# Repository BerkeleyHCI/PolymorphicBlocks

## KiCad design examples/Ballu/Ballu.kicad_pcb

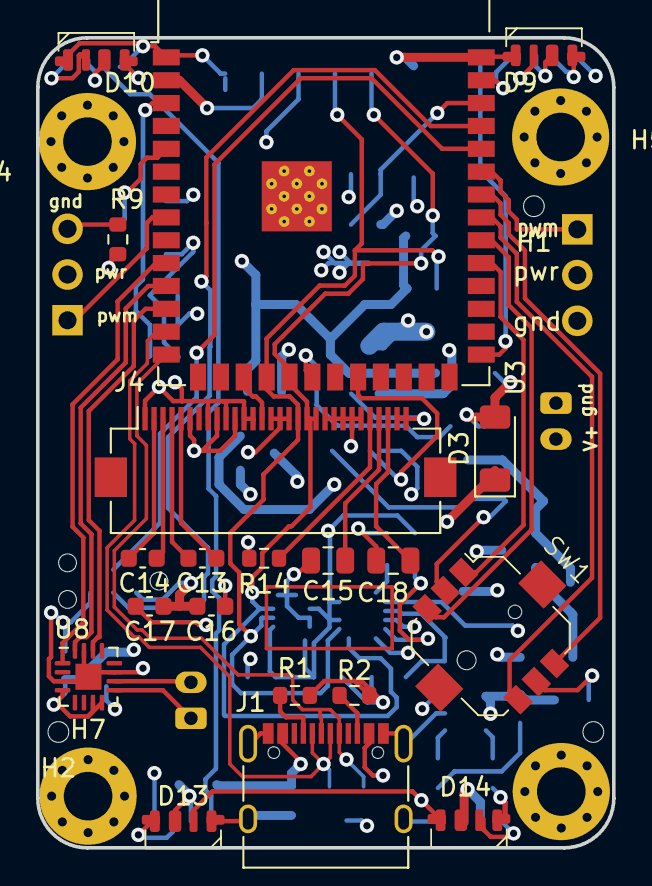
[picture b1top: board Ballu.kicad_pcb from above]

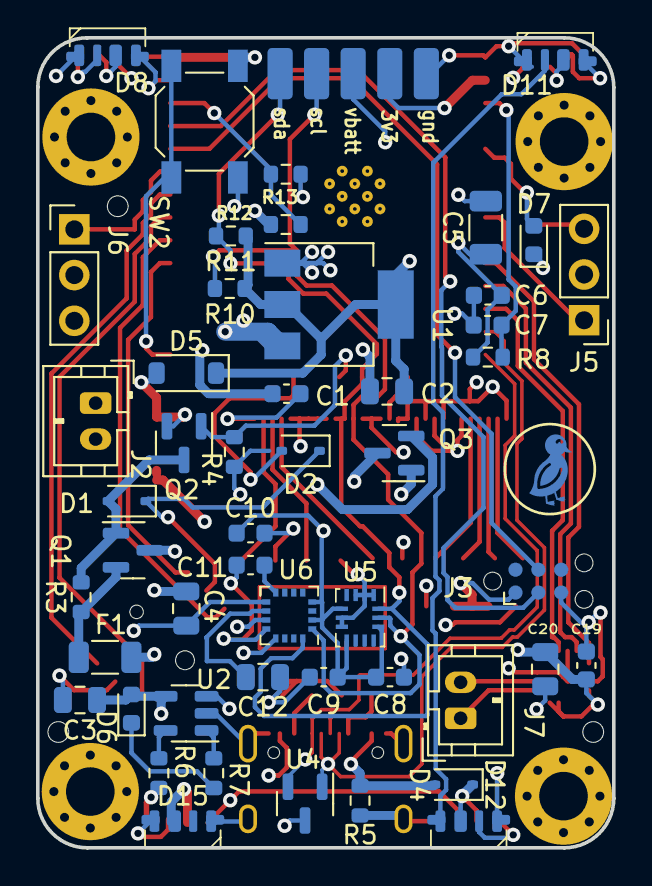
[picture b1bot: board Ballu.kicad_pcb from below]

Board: 4 copper layers, 32.0 x 45.0 mm, 83 parts (55 on the bottom side), 57 nets.

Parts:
C1, C6, C7, C8, C9, C10, C11, C13, C14, C16, C17, C19: C_0603_1608Metric
C2, C3, C4, C12, C15, C18, C20: C_0805_2012Metric
C5: C_1206_3216Metric
D1, D2: 30V 370mV@1mA 30mA SOD-323 Schottky Barrier Diode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; D_SOD-323
D3: D_MiniMELF
D4: 10V 1V@600mA 3A SOD-323 Schottky Barrier Diodes (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; D_SOD-323
D5: 5?A@1V 90? Single 3.6V~3.8V 350mW 3.4V SOD-123 Ze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; D_SOD-123
D6: LED_0603_1608Metric
D7: Red 615~630nm 1.9~2.2V 0603 Light Emitting Diodes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; LED_0603_1608Metric
D8, D9, D10, D11, D12, D13, D14, D15: SK6812 SIDE-A; LED_SK6812-SIDE-A
F1: 6V 2A 100A 4A 1206 Resettable Fuses ROHS; R_1206_3216Metric
H1, H2, H3: JlcToolingHole_1.152mm
H4, H5, H6, H7: M2.5; MountingHole_2.7mm_M2.5_Pad_Via
J1: COM-15111; USB_C_Receptacle_XKB_U262-16XN-4BVC11
J2, J7: B2B-PH-K; JST_PH_B2B-PH-K_1x02_P2.00mm_Vertical
J3: Tag-Connect_TC2030-IDC-NL_2x03_P1.27mm_Vertical
J4: AFC01-S30FCA-00; Hirose_FH12-30S-0.5SH_1x30-1MP_P0.50mm_Horizontal
J5, J6: PinHeader2.54 1x3; PinHeader_1x03_P2.54mm_Vertical
Q1: 20V 3.1A 860mW 112m?@4.5V,2.8A 1V@250?A P Channel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; SOT-23
Q2: 60V 115mA 200mW 7.5?@10V,500mA 2.5V@250?A N Chann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; SOT-23
Q3: 30V 4A 44m?@10V,4.3A 1.4W 1.3V@250?A P Channel SO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; SOT-23
R1, R2, R3, R4, R5, R6, R7, R8, R9, R10, R11, R12, R13, R14: R_0603_1608Metric
SW1: SKRHABE010; DirectionSwitch_Alps_SKRH
SW2: 5.1mm switch; SW_SPST_SKQG_WithoutStem
TP1: gnd; TestPoint_TE_RCT_0805
TP2: gate.vbatt; TestPoint_TE_RCT_0805
TP3: preg_3v3._pwr_out_link; TestPoint_TE_RCT_0805
TP4: i2c.scl; TestPoint_TE_RCT_0805
TP5: i2c.sda; TestPoint_TE_RCT_0805
U1: LDL1117S33R; SOT-223-3_TabPin2
U2: MCP73831T-2ACI/OT; SOT-23-5
U3: ESP32-S3-WROOM-1-N16R8; ESP32-S3-WROOM-1
U4: PESD5V0X1BT; SOT-23
U5: LSM6DS3TR-C; Bosch_LGA-14_3x2.5mm_P0.5mm
U6: QMC5883L; LGA-16_3x3mm_P0.5mm
U7: ER-OLED-0.96-1.1; Lcd_Er_Oled0.96_1.1_Outline
U8: MAX98357AETE+T; QFN-16-1EP_3x3mm_P0.5mm_EP1.45x1.45mm
svg2mod: G***; Symbol_DucklingSolid

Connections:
batt.pwr: C4.1, F1.1, J2.2, U2.3
batt_sense.output: R12.2, R13.1, U3.38
charger.charge_led.res.a: D6.1, R7.1
charger.charge_led.signal: R7.2, U2.1
charger.charger.prog_res.a: R6.1, U2.5
gate.btn_out: D2.2, U3.22
gate.control: Q2.1, R4.2, U3.20
gate.dir.center: D1.1, D2.1, SW1.2
gate.dir_a: SW1.1, U3.31
gate.dir_b: SW1.4, U3.34
gate.dir_c: SW1.3, U3.32
gate.dir_d: SW1.6, U3.33
gate.fuse.pwr_out: F1.2, Q1.2, R3.1
gate.gate.pull_res.b: D1.2, Q1.1, Q2.3, R3.2
gate.vbatt: D3.1, Q1.3, Q3.3, TP2.1
gnd: C1.2, C2.2, C3.2, C4.2, C5.2, C6.2, C7.2, C8.2, C9.2, C10.2, C12.2, C15.2, C16.2, C17.2, C18.2, C19.2, C20.2, D3.2, D5.2, D8.4, D9.4, D10.4, D11.4, D12.4, D13.4, D14.4, D15.4, J1.A1, J1.A12, J1.B1, J1.B12, J1.S1, J2.1, J3.5, J4.1, J4.8, J4.10, J4.12, J4.13, J4.15, J4.16, J4.17, J4.21, J4.22, J4.23, J4.24, J4.25, J4.29, J4.30, J5.3, J6.3, Q2.2, R1.1, R2.1, R4.1, R5.2, R6.2, R9.2, R13.2, R14.2, SW1.5, SW2.2, TP1.1, U1.1, U2.2, U3.1, U3.40, U3.41, U4.3, U5.1, U5.2, U5.3, U5.6, U5.7, U6.9, U6.11, U8.3, U8.11, U8.15, U8.17
i2c_chain_0.scl: J4.18, R10.2, TP4.1, U3.18, U5.13, U6.1
i2c_chain_0.sda: J4.19, J4.20, R11.2, TP5.1, U3.19, U5.14, U6.16
led.res.a: D7.1, R9.1
led.signal: D7.2, U3.5
mag.c1.pos: C12.1, U6.10
mag.set_cap.neg: C11.2, U6.12
mag.set_cap.pos: C11.1, U6.8
mcu.program_boot_node: SW2.1, U3.27
mcu.program_en_node: C7.1, R8.2, U3.3
mcu.program_uart_node.a_tx: J3.3, U3.37
mcu.program_uart_node.b_tx: J3.4, U3.36
npx_side.din: D8.1, U3.39
npx_side.led[0].dout: D8.3, D9.1
npx_side.led[1].dout: D9.3, D10.1
npx_side.led[2].dout: D10.3, D11.1
npx_side.led[3].dout: D11.3, D12.1
npx_side.led[4].dout: D12.3, D13.1
npx_side.led[5].dout: D13.3, D14.1
npx_side.led[6].dout: D14.3, D15.1
oled.c1_cap.neg: C13.2, J4.5
oled.c1_cap.pos: C13.1, J4.4
oled.c2_cap.neg: C14.2, J4.3
oled.c2_cap.pos: C14.1, J4.2
oled.device.vcc: C18.1, J4.28
oled.device.vcomh: C15.1, J4.27
oled.iref_res.a: J4.26, R14.1
oled.reset: J4.14, U3.17
pwr: C1.1, D4.1, D8.2, D9.2, D10.2, D11.2, D12.2, D13.2, D14.2, D15.2, J5.2, J6.2, Q3.2, R12.1, U1.3
servo[0].pwm: J5.1, U3.8
servo[1].pwm: J6.1, U3.35
spk_drv.i2s.sck: U3.11, U8.16
spk_drv.i2s.sd: U3.10, U8.1
spk_drv.i2s.ws: U3.12, U8.14
spk_drv.out.a: J7.1, U8.9
spk_drv.out.b: J7.2, U8.10
usb.conn.A5: J1.A5, R1.2
usb.conn.B5: J1.B5, R2.2
usb_chain_0.d_N: J1.A7, J1.B7, U3.13, U4.1
usb_chain_0.d_P: J1.A6, J1.B6, U3.14, U4.2
v3v3: C2.1, C5.1, C6.1, C8.1, C9.1, C10.1, C16.1, C17.1, C19.1, C20.1, D5.1, J3.1, J4.6, J4.9, J4.11, R8.1, R10.1, R11.1, TP3.1, U1.2, U3.2, U5.5, U5.8, U5.12, U6.2, U6.4, U6.13, U8.4, U8.7, U8.8
vusb: C3.1, D4.2, D6.2, J1.A4, J1.A9, J1.B4, J1.B9, Q3.1, R5.1, U2.4

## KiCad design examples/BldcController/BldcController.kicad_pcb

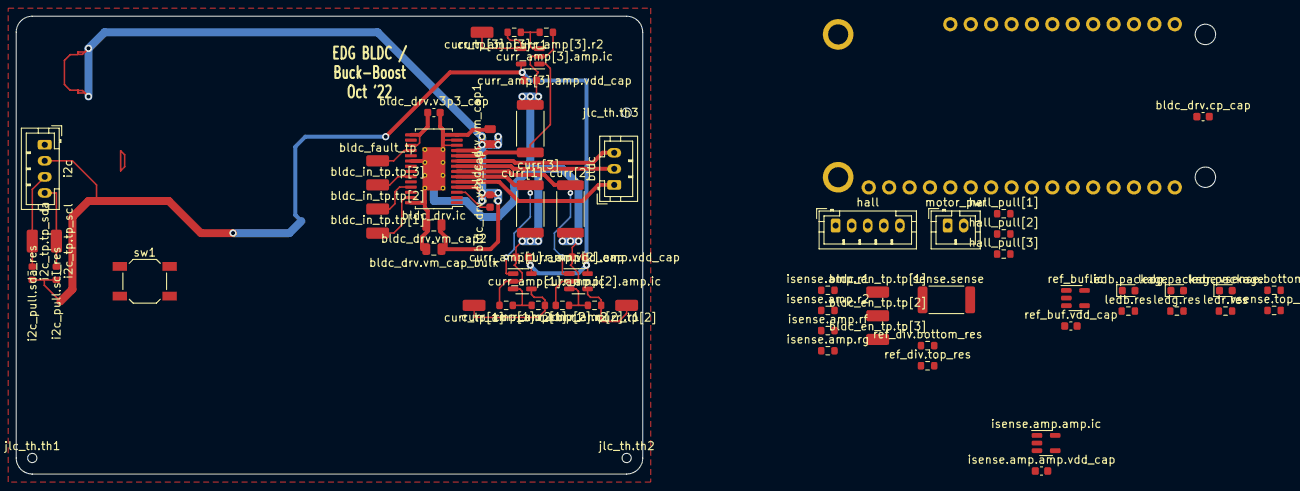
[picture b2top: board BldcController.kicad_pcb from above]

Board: 2 copper layers, 78.0 x 57.0 mm, 67 parts (0 on the bottom side), 47 nets.

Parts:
bldc: B3B-PH-K (JST); JST_PH_B3B-PH-K_1x03_P2.00mm_Vertical
bldc_drv.cp_cap, bldc_drv.v3p3_cap, bldc_drv.vcp_cap: C_0603_1608Metric
bldc_drv.ic: DRV8313PWP (Texas Instruments); HTSSOP-28-1EP_4.4x9.7mm_P0.65mm_EP2.85x5.4mm_ThermalVias
bldc_drv.vm_cap1, bldc_drv.vm_cap2, bldc_drv.vm_cap_bulk: C_0805_2012Metric
bldc_en_tp.tp[1]: 5015 (Keystone) - _mcu_gpio_bldc_en_link.1; TestPoint_TE_RCT_0805
bldc_en_tp.tp[2]: 5015 (Keystone) - _mcu_gpio_bldc_en_link.2; TestPoint_TE_RCT_0805
bldc_en_tp.tp[3]: 5015 (Keystone) - _mcu_gpio_bldc_en_link.3; TestPoint_TE_RCT_0805
bldc_fault_tp: 5015 (Keystone) - _mcu_gpio_bldc_fault_link; TestPoint_TE_RCT_0805
bldc_in_tp.tp[1]: 5015 (Keystone) - _mcu_gpio_bldc_in_link.1; TestPoint_TE_RCT_0805
bldc_in_tp.tp[2]: 5015 (Keystone) - _mcu_gpio_bldc_in_link.2; TestPoint_TE_RCT_0805
bldc_in_tp.tp[3]: 5015 (Keystone) - _mcu_gpio_bldc_in_link.3; TestPoint_TE_RCT_0805
curr[1], curr[2], curr[3]: R_2512_6332Metric
curr_amp[1].amp.ic, curr_amp[2].amp.ic, curr_amp[3].amp.ic: LMV321 (Texas Instruments); SOT-23-5
curr_amp[1].amp.vdd_cap, curr_amp[2].amp.vdd_cap, curr_amp[3].amp.vdd_cap: C_0603_1608Metric
curr_amp[1].r1, curr_amp[1].r2, curr_amp[2].r1, curr_amp[2].r2, curr_amp[3].r1, curr_amp[3].r2: R_0603_1608Metric
curr_tp[1]: 5015 (Keystone) - _curr_amp[1]_output_link; TestPoint_TE_RCT_0805
curr_tp[2]: 5015 (Keystone) - _curr_amp[2]_output_link; TestPoint_TE_RCT_0805
curr_tp[3]: 5015 (Keystone) - _curr_amp[3]_output_link; TestPoint_TE_RCT_0805
hall: B5B-PH-K (JST); JST_PH_B5B-PH-K_1x05_P2.00mm_Vertical
hall_pull[1], hall_pull[2], hall_pull[3]: R_0603_1608Metric
i2c: B4B-PH-K (JST); JST_PH_B4B-PH-K_1x04_P2.00mm_Vertical
i2c_pull.scl_res, i2c_pull.sda_res: R_0603_1608Metric
i2c_tp.tp_scl: 5015 (Keystone) - _mcu_i2c_i2c_link.scl; TestPoint_TE_RCT_0805
i2c_tp.tp_sda: 5015 (Keystone) - i2c_tp._io_sda_link; TestPoint_TE_RCT_0805
isense.amp.amp.ic: LMV321 (Texas Instruments); SOT-23-5
isense.amp.amp.vdd_cap: C_0603_1608Metric
isense.amp.r1, isense.amp.r2, isense.amp.rf, isense.amp.rg: R_0603_1608Metric
isense.sense: R_2512_6332Metric
jlc_th.th1, jlc_th.th2, jlc_th.th3: JlcToolingHole_1.152mm
ledb.package: LED_0603_1608Metric
ledb.res: R_0603_1608Metric
ledg.package: LED_0603_1608Metric
ledg.res: R_0603_1608Metric
ledr.package: KT-0603R (Hubei KENTO Elec) - Red 615~630nm 1.9~2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; LED_0603_1608Metric
ledr.res: R_0603_1608Metric
mcu: Feather nRF52840 Express (Adafruit); FEATHERWING_NODIM
motor_pwr: B2B-PH-K (JST); JST_PH_B2B-PH-K_1x02_P2.00mm_Vertical
ref_buf.ic: LMV321 (Texas Instruments); SOT-23-5
ref_buf.vdd_cap: C_0603_1608Metric
ref_div.bottom_res, ref_div.top_res: R_0603_1608Metric
sw1: 5.1mm switch; SW_SPST_SKQG_WithoutStem
vsense.bottom_res, vsense.top_res: R_0603_1608Metric

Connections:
bldc_drv.cp_cap.neg: bldc_drv.cp_cap.2, bldc_drv.ic.1
bldc_drv.cp_cap.pos: bldc_drv.cp_cap.1, bldc_drv.ic.2
bldc_drv.ic.v3p3: bldc_drv.ic.15, bldc_drv.ic.17, bldc_drv.v3p3_cap.1
bldc_drv.nfault: bldc_drv.ic.18, bldc_fault_tp.1, mcu.18
bldc_drv.nreset: bldc_drv.ic.16, mcu.25
bldc_drv.outs.1: bldc.1, bldc_drv.ic.5
bldc_drv.outs.2: bldc.2, bldc_drv.ic.8
bldc_drv.outs.3: bldc.3, bldc_drv.ic.9
bldc_drv.vcp_cap.pos: bldc_drv.ic.3, bldc_drv.vcp_cap.1
curr[1].pwr_out: bldc_drv.ic.6, curr[1].2, curr_amp[1].amp.ic.1
curr[2].pwr_out: bldc_drv.ic.7, curr[2].2, curr_amp[2].amp.ic.1
curr[3].pwr_out: bldc_drv.ic.10, curr[3].2, curr_amp[3].amp.ic.1
curr_amp[1].output: curr_amp[1].amp.ic.4, curr_amp[1].r1.1, curr_tp[1].1, mcu.7
curr_amp[1].r1.b: curr_amp[1].amp.ic.3, curr_amp[1].r1.2, curr_amp[1].r2.1
curr_amp[2].output: curr_amp[2].amp.ic.4, curr_amp[2].r1.1, curr_tp[2].1, mcu.8
curr_amp[2].r1.b: curr_amp[2].amp.ic.3, curr_amp[2].r1.2, curr_amp[2].r2.1
curr_amp[3].output: curr_amp[3].amp.ic.4, curr_amp[3].r1.1, curr_tp[3].1, mcu.10
curr_amp[3].r1.b: curr_amp[3].amp.ic.3, curr_amp[3].r1.2, curr_amp[3].r2.1
gnd: bldc_drv.ic.12, bldc_drv.ic.13, bldc_drv.ic.14, bldc_drv.ic.20, bldc_drv.ic.28, bldc_drv.ic.29, bldc_drv.v3p3_cap.2, bldc_drv.vm_cap1.2, bldc_drv.vm_cap2.2, bldc_drv.vm_cap_bulk.2, curr[1].1, curr[2].1, curr[3].1, curr_amp[1].amp.ic.2, curr_amp[1].amp.vdd_cap.2, curr_amp[1].r2.2, curr_amp[2].amp.ic.2, curr_amp[2].amp.vdd_cap.2, curr_amp[2].r2.2, curr_amp[3].amp.ic.2, curr_amp[3].amp.vdd_cap.2, curr_amp[3].r2.2, hall.5, i2c.1, isense.amp.amp.ic.2, isense.amp.amp.vdd_cap.2, ledb.res.2, ledg.res.2, ledr.res.2, mcu.4, motor_pwr.1, ref_buf.ic.2, ref_buf.vdd_cap.2, ref_div.bottom_res.2, sw1.2, vsense.bottom_res.2
hall.u: hall.2, hall_pull[1].2, mcu.20
hall.v: hall.3, hall_pull[2].2, mcu.24
hall.w: hall.4, hall_pull[3].2, mcu.19
i2c_pull.i2c.scl: i2c.4, i2c_pull.scl_res.2, i2c_tp.tp_scl.1, mcu.21
i2c_pull.i2c.sda: i2c.3, i2c_pull.sda_res.2, i2c_tp.tp_sda.1, mcu.22
isense.amp.r1.b: isense.amp.amp.ic.3, isense.amp.r1.2, isense.amp.rf.2
isense.amp.r2.b: isense.amp.amp.ic.1, isense.amp.r2.2, isense.amp.rg.2
isense.out: isense.amp.amp.ic.4, isense.amp.rf.1, mcu.9
isense.pwr_out: bldc_drv.ic.4, bldc_drv.ic.11, bldc_drv.vcp_cap.2, bldc_drv.vm_cap1.1, bldc_drv.vm_cap2.1, bldc_drv.vm_cap_bulk.1, isense.amp.r1.1, isense.sense.2
isense.ref: isense.amp.rg.1, ref_buf.ic.3, ref_buf.ic.4
ledb.res.a: ledb.package.1, ledb.res.1
ledb.signal: ledb.package.2, mcu.23
ledg.res.a: ledg.package.1, ledg.res.1
ledg.signal: ledg.package.2, mcu.6
ledr.res.a: ledr.package.1, ledr.res.1
ledr.signal: ledr.package.2, mcu.16
mcu.gpio.bldc_en_1: bldc_drv.ic.26, bldc_en_tp.tp[1].1, mcu.17
mcu.gpio.bldc_en_2: bldc_drv.ic.24, bldc_en_tp.tp[2].1, mcu.11
mcu.gpio.bldc_en_3: bldc_drv.ic.22, bldc_en_tp.tp[3].1, mcu.15
mcu.gpio.bldc_in_1: bldc_drv.ic.27, bldc_in_tp.tp[1].1, mcu.12
mcu.gpio.bldc_in_2: bldc_drv.ic.25, bldc_in_tp.tp[2].1, mcu.13
mcu.gpio.bldc_in_3: bldc_drv.ic.23, bldc_in_tp.tp[3].1, mcu.14
motor_pwr.pwr: isense.amp.r2.1, isense.sense.1, motor_pwr.2, vsense.top_res.1
ref_div.output: ref_buf.ic.1, ref_div.bottom_res.1, ref_div.top_res.2
sw1.out: mcu.5, sw1.1
v3v3: curr_amp[1].amp.ic.5, curr_amp[1].amp.vdd_cap.1, curr_amp[2].amp.ic.5, curr_amp[2].amp.vdd_cap.1, curr_amp[3].amp.ic.5, curr_amp[3].amp.vdd_cap.1, hall_pull[1].1, hall_pull[2].1, hall_pull[3].1, i2c.2, i2c_pull.scl_res.1, i2c_pull.sda_res.1, isense.amp.amp.ic.5, isense.amp.amp.vdd_cap.1, mcu.2, ref_buf.ic.5, ref_buf.vdd_cap.1, ref_div.top_res.1
vsense.output: mcu.3, vsense.bottom_res.1, vsense.top_res.2
vusb: hall.1, mcu.26

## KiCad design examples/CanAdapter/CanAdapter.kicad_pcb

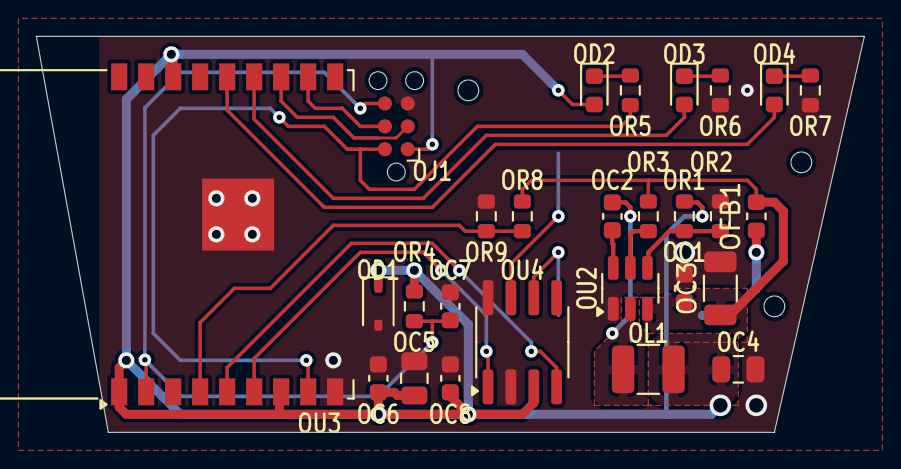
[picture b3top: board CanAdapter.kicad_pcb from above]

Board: 2 copper layers, 46.0 x 22.0 mm, 31 parts (1 on the bottom side), 22 nets.

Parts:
OC1: reg_3v3.hf_in_cap; C_0603_1608Metric
OC2: reg_3v3.boot_cap; C_0603_1608Metric
OC3: reg_3v3.power_path.in_cap; C_1206_3216Metric
OC4: reg_3v3.power_path.out_cap; C_0805_2012Metric
OC5: mcu.vcc_cap0; C_0805_2012Metric
OC6: mcu.vcc_cap1; C_0603_1608Metric
OC7: mcu.en_pull.c; C_0603_1608Metric
OC8: can.vdd_cap; C_0603_1608Metric
OD1: prot_3v3; D_SOD-323
OD2: ledr.package; LED_0603_1608Metric
OD3: ledg.package; LED_0603_1608Metric
OD4: ledw.package; LED_0603_1608Metric
OFB1: ferrite; L_0603_1608Metric
OH1: jlc_th.th1; JlcToolingHole_1.152mm
OH2: jlc_th.th2; JlcToolingHole_1.152mm
OH3: jlc_th.th3; JlcToolingHole_1.152mm
OJ1: mcu.prog; Tag-Connect_TC2030-IDC-NL_2x03_P1.27mm_Vertical
OL1: reg_3v3.power_path.inductor; L_1210_3225Metric
OR1: reg_3v3.fb.top_res; R_0603_1608Metric
OR2: reg_3v3.fb.bottom_res; R_0603_1608Metric
OR3: reg_3v3.en_res; R_0603_1608Metric
OR4: mcu.en_pull.r; R_0603_1608Metric
OR5: ledr.res; R_0603_1608Metric
OR6: ledg.res; R_0603_1608Metric
OR7: ledw.res; R_0603_1608Metric
OR8: vobd_sense.top_res; R_0603_1608Metric
OR9: vobd_sense.bottom_res; R_0603_1608Metric
OU1: obd; J1962
OU2: reg_3v3.ic; SOT-23-6
OU3: mcu.ic; ESP-WROOM-02
OU4: can.ic; SOIC-8_3.9x4.9mm_P1.27mm

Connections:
Ocan.can.canh: OU1.6, OU4.7
Ocan.can.canl: OU1.14, OU4.6
Ocan.controller.rxd: OU3.5, OU4.4
Ocan.controller.txd: OU3.6, OU4.1
Ognd: OC1.2, OC3.2, OC4.2, OC5.2, OC6.2, OC7.2, OC8.2, OD1.2, OJ1.5, OR2.2, OR6.2, OR7.2, OR9.2, OU1.5, OU2.1, OU3.9, OU3.19, OU4.2, OU4.8
Oledg.res.a: OD3.1, OR6.1
Oledg.signal: OD3.2, OU3.13
Oledr.res.a: OD2.1, OR5.1
Oledw.res.a: OD4.1, OR7.1
Oledw.signal: OD4.2, OU3.14
Omcu.program_boot_node: OJ1.2, OR5.2, OU3.8
Omcu.program_en_node: OC7.1, OJ1.6, OR4.2, OU3.2
Omcu.program_uart_node.a_tx: OJ1.3, OU3.12
Omcu.program_uart_node.b_tx: OJ1.4, OU3.11
Oobd.pwr: OFB1.1, OU1.16
Oreg_3v3.boot_cap.neg: OC2.2, OL1.1, OU2.2
Oreg_3v3.boot_cap.pos: OC2.1, OU2.6
Oreg_3v3.en_res.b: OR3.2, OU2.5
Oreg_3v3.fb.output: OR1.2, OR2.1, OU2.4
Ov3v3: OC4.1, OC5.1, OC6.1, OC8.1, OD1.1, OD2.2, OJ1.1, OL1.2, OR1.1, OR4.1, OU3.1, OU3.7, OU3.16, OU4.3
Ovobd: OC1.1, OC3.1, OFB1.2, OR3.1, OR8.1, OU2.3
Ovobd_sense.output: OR8.2, OR9.1, OU3.4

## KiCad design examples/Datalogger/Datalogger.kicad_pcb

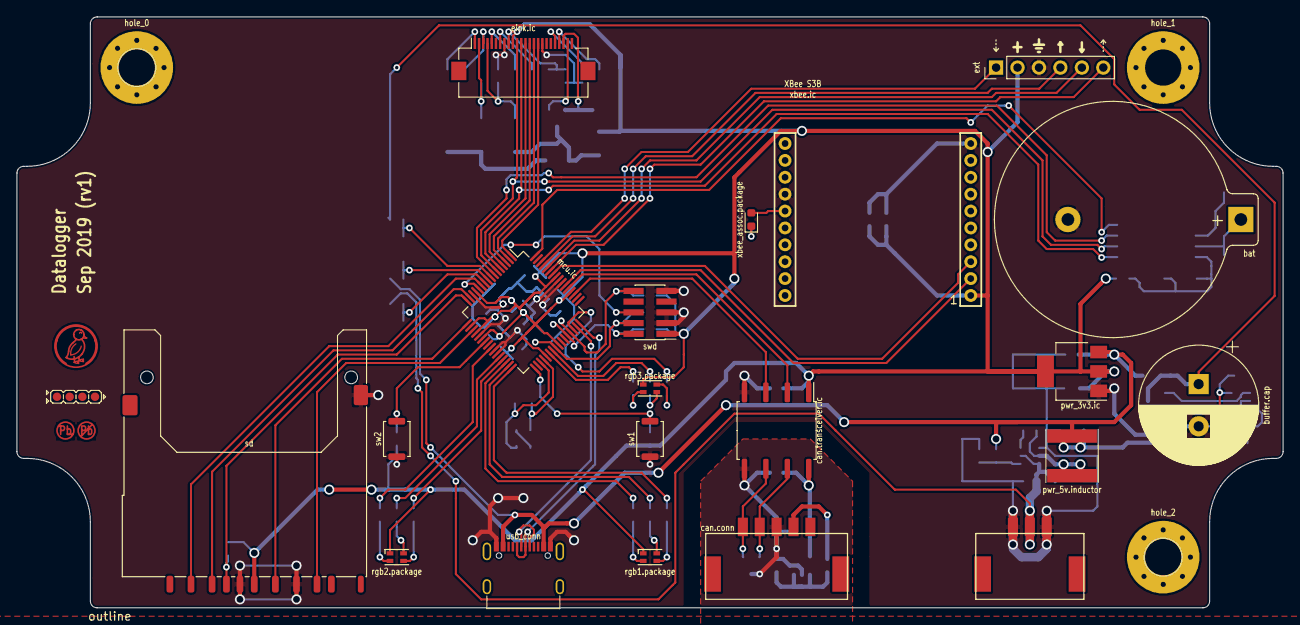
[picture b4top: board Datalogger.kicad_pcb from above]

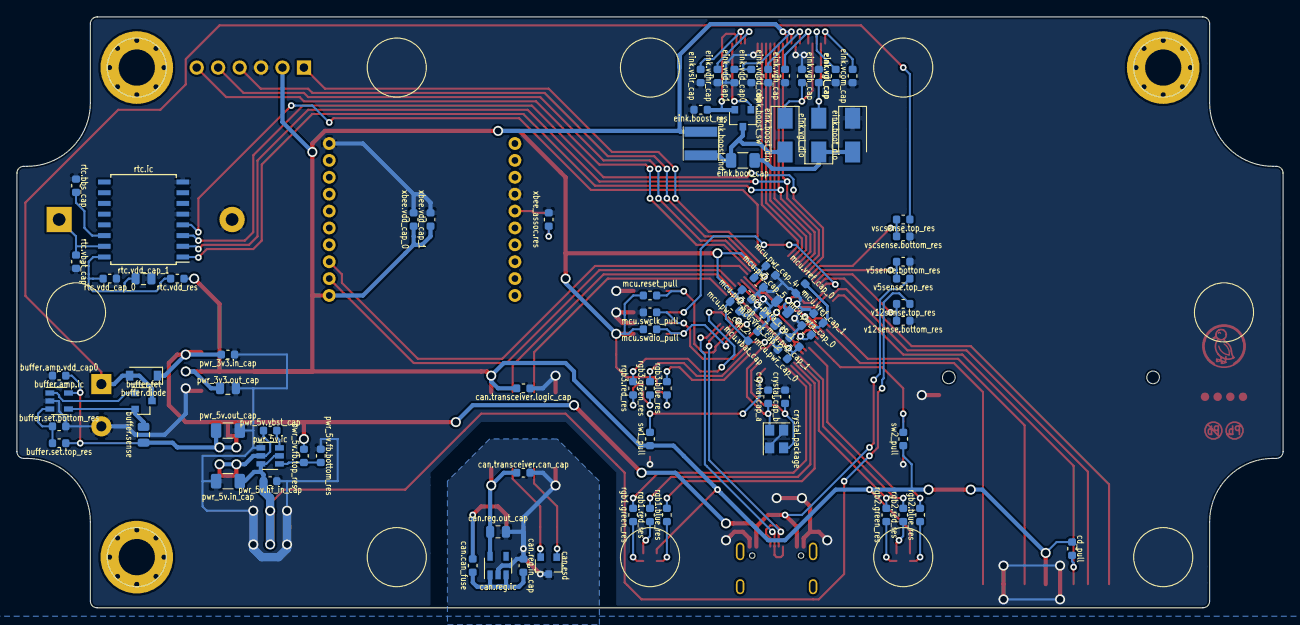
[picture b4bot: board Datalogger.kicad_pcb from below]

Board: 2 copper layers, 150.0 x 70.0 mm, 112 parts (85 on the bottom side), 86 nets.

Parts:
bat: CR2032; BatteryHolder_Keystone_106_1x20mm
buffer.amp.ic: MCP6001T; SOT-23-5
buffer.amp.vdd_cap0: 0.1µF, 50V, CL10B104KB8NNNC; C_0603_1608Metric
buffer.cap: DBN-5R5D334T; CP_Radial_D14.0mm_P5.00mm
buffer.diode: MBR0520L; D_SOD-123
buffer.fet: SQ2301ES-T1_GE3; SOT-23
buffer.sense: 0.47, 1%, 0.125W; R_0805_2012Metric
buffer.set.bottom_res: 220000, 1%, 0.1W; R_0603_1608Metric
buffer.set.top_res: 10000, 1%, 0.1W; R_0603_1608Metric
can.can_fuse: 0ZCM0005FF2G; R_0603_1608Metric
can.conn: Duraclik; Molex_DuraClik_vert_5pin
can.esd: PESD1CAN,215; SOT-23
can.reg.ic: AP2204K-5.0; SOT-23-5
can.reg.in_cap: 1µF, 25V, CL10A105KA8NNNC; C_0603_1608Metric
can.reg.out_cap: 2.2µF, 10V, CL21B225KPFNNNE; C_0805_2012Metric
can.transceiver.can_cap, can.transceiver.logic_cap: 0.1µF, 50V, CL10B104KB8NNNC; C_0603_1608Metric
can.transceiver.ic: ISO1050DUB; SOP-8_6.62x9.15mm_P2.54mm
cd_pull: 4700, 1%, 0.1W; R_0603_1608Metric
crystal.cap_a, crystal.cap_b: 18pF, 50V, CC0603GRNPO9BN180; C_0603_1608Metric
crystal.package: 7V-12.000MAHE-T; Oscillator_SMD_Abracon_ASE-4Pin_3.2x2.5mm
duck: Duck; Symbol_Duckling
eink.boost_dio, eink.boot_dio, eink.vgl_dio: CDBA240LL-HF; D_SMA
eink.boost_ind: 10µH, 840mA, NR4018T100M; L_Taiyo-Yuden_NR-40xx
eink.boost_res: 0.47, 1%, 0.1W; R_0603_1608Metric
eink.boost_sw: DMN3404L-7; SOT-23
eink.boot_cap: 22µF, 16V, CL31A226MOCLNNC; C_1206_3216Metric
eink.ic: E2154FS091, FH12-24S-0.5SH(55); Hirose_FH12-24S-0.5SH_1x24-1MP_P0.50mm_Horizontal
eink.vcom_cap, eink.vddd_cap, eink.vdh_cap, eink.vdhr_cap, eink.vdl_cap, eink.vgh_cap, eink.vgl_cap, eink.vslr_cap: 1µF, 25V, CL10A105KA8NNNC; C_0603_1608Metric
eink.vdd_cap0: 0.1µF, 50V, CL10B104KB8NNNC; C_0603_1608Metric
eink.vdd_cap1: 1µF, 10V, CL10A105KP8NNNC; C_0603_1608Metric
ext: BlueSMiRF; PinHeader_1x06_P2.54mm_Vertical
hole_0, hole_1, hole_2: M4; MountingHole_4.3mm_M4_Pad_Via
id: IdDots4; Indicator_IdDots_4
leadfree: LeadFree; Indicator_LeadFree
mcu.ic: LPC1549JBD64; LQFP-64_10x10mm_P0.5mm
mcu.pwr_cap_0, mcu.pwr_cap_2, mcu.pwr_cap_4, mcu.pwra_cap_0, mcu.vbat_cap, mcu.vref_cap_0, mcu.vref_cap_1: 0.1µF, 50V, CL10B104KB8NNNC; C_0603_1608Metric
mcu.pwr_cap_1, mcu.pwr_cap_3, mcu.pwr_cap_5: 10000pF, 50V, CL10B103KB8NNNC; C_0603_1608Metric
mcu.pwra_cap_1, mcu.vref_cap_2: 10µF, 10V, CL21A106KPFNNNE; C_0805_2012Metric
mcu.reset_pull, mcu.swclk_pull, mcu.swdio_pull: 10000, 1%, 0.1W; R_0603_1608Metric
outline: PN1332_Panel; Outline_150mm_70mm_PNX-91432
pwr_3v3.ic: LD1117V33; SOT-223-3_TabPin2
pwr_3v3.in_cap, pwr_5v.hf_in_cap, pwr_5v.vbst_cap: 0.1µF, 50V, CL10B104KB8NNNC; C_0603_1608Metric
pwr_3v3.out_cap: 10µF, 10V, CL21A106KPFNNNE; C_0805_2012Metric
pwr_5v.fb.bottom_res: 1200, 1%, 0.1W; R_0603_1608Metric
pwr_5v.fb.top_res: 6800, 1%, 0.1W; R_0603_1608Metric
pwr_5v.ic: TPS561201; SOT-23-6
pwr_5v.in_cap: 22µF, 16V, CL31A226MOCLNNC; C_1206_3216Metric
pwr_5v.inductor: 10µH, 2.5A, NR6045T100M; L_Taiyo-Yuden_NR-60xx
pwr_5v.out_cap: 22µF, 6.3V, CL31A226MQHNNNE; C_1206_3216Metric
pwr_conn: Duraclik; Molex_DuraClik_vert_3pin
rgb1.blue_res, rgb1.green_res, rgb1.red_res, rgb2.blue_res, rgb2.green_res, rgb2.red_res, rgb3.blue_res, rgb3.green_res, rgb3.red_res: 1000, 1%, 0.1W; R_0603_1608Metric
rgb1.package, rgb2.package, rgb3.package: LED_RGB_0606
rtc.bbs_cap, rtc.vbat_cap, rtc.vdd_cap_0: 0.1µF, 50V, CL10B104KB8NNNC; C_0603_1608Metric
rtc.ic: PCF2129T; SOIC-16W_7.5x10.3mm_P1.27mm
rtc.vdd_cap_1: 4.7µF, 6.3V, CL21A475KQFNNNG; C_0805_2012Metric
rtc.vdd_res: 330, 1%, 0.1W; R_0603_1608Metric
sd: SD Socket, Kyocera 145638009511859+; SD_Kyocera_145638009511859+
sw1, sw2: switch; SW_Push_SPST_NO_Alps_SKRK
sw1_pull, sw2_pull: 4700, 1%, 0.1W; R_0603_1608Metric
swd: SWD; PinHeader_2x05_P1.27mm_Vertical_SMD
usb_conn: USB-C; USB_C_Receptacle_BSC_A40-00119
v5sense.bottom_res: 15000, 1%, 0.1W; R_0603_1608Metric
v5sense.top_res: 10000, 1%, 0.1W; R_0603_1608Metric
v12sense.bottom_res: 1500, 1%, 0.1W; R_0603_1608Metric
v12sense.top_res: 4700, 1%, 0.1W; R_0603_1608Metric
vscsense.bottom_res: 15000, 1%, 0.1W; R_0603_1608Metric
vscsense.top_res: 10000, 1%, 0.1W; R_0603_1608Metric
xbee.ic: XBee S3B; XBEE
xbee.vdd_cap_0: 1µF, 10V, CL10A105KP8NNNC; C_0603_1608Metric
xbee.vdd_cap_1: 47pF, 100V, CL10C470JC8NNNC; C_0603_1608Metric
xbee_assoc.package: LED_0603_1608Metric
xbee_assoc.res: 1000, 1%, 0.1W; R_0603_1608Metric

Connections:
buffer.amp.inn: buffer.amp.ic.4, buffer.fet.2, buffer.sense.2
buffer.amp.inp: buffer.amp.ic.3, buffer.set.bottom_res.1, buffer.set.top_res.2
buffer.fet.gate: buffer.amp.ic.1, buffer.fet.1
can.can.canh: can.conn.4, can.esd.2, can.transceiver.ic.7
can.can.canl: can.conn.5, can.esd.1, can.transceiver.ic.6
can.can_gnd: can.conn.3, can.esd.3, can.reg.ic.2, can.reg.in_cap.2, can.reg.out_cap.2, can.transceiver.can_cap.2, can.transceiver.ic.5
can.can_pwr: can.can_fuse.1, can.conn.2
can.controller.rxd: can.transceiver.ic.2, mcu.ic.53
can.reg.pwr_in: can.can_fuse.2, can.reg.ic.1, can.reg.ic.3, can.reg.in_cap.1
can.reg.pwr_out: can.reg.ic.5, can.reg.out_cap.1, can.transceiver.can_cap.1, can.transceiver.ic.8
cd_pull.b: cd_pull.2, mcu.ic.16, sd.10
eink.boost_sw.source: eink.boost_res.1, eink.boost_sw.2, eink.ic.22
eink.boot_cap.pos: eink.boost_dio.2, eink.boost_ind.2, eink.boost_sw.3, eink.boot_cap.1
eink.boot_dio.anode: eink.boot_cap.2, eink.boot_dio.2, eink.vgl_dio.1
eink.ic.gdr: eink.boost_sw.1, eink.ic.23
eink.ic.vcom: eink.ic.1, eink.vcom_cap.1
eink.ic.vddd: eink.ic.7, eink.vddd_cap.1
eink.ic.vgh: eink.boost_dio.1, eink.ic.4, eink.vgh_cap.1
eink.spi.miso: mcu.ic.7, rtc.ic.3
eink.vdh_cap.pos: eink.ic.5, eink.vdh_cap.1
eink.vdhr_cap.pos: eink.ic.20, eink.vdhr_cap.1
eink.vdl_cap.pos: eink.ic.3, eink.vdl_cap.1
eink.vgl_cap.pos: eink.ic.2, eink.vgl_cap.1, eink.vgl_dio.2
eink.vslr_cap.pos: eink.ic.21, eink.vslr_cap.1
ext.cts: ext.1, mcu.ic.62
ext.data.rx: ext.5, mcu.ic.60
ext.data.tx: ext.4, mcu.ic.61
gnd: bat.2, buffer.amp.ic.2, buffer.amp.vdd_cap0.2, buffer.cap.2, buffer.set.bottom_res.2, can.transceiver.ic.4, can.transceiver.logic_cap.2, crystal.cap_a.2, crystal.cap_b.2, crystal.package.2, crystal.package.4, eink.boost_res.2, eink.boot_dio.1, eink.ic.8, eink.ic.17, eink.vcom_cap.2, eink.vdd_cap0.2, eink.vdd_cap1.2, eink.vddd_cap.2, eink.vdh_cap.2, eink.vdhr_cap.2, eink.vdl_cap.2, eink.vgh_cap.2, eink.vgl_cap.2, eink.vslr_cap.2, ext.3, mcu.ic.14, mcu.ic.21, mcu.ic.26, mcu.ic.27, mcu.ic.55, mcu.ic.56, mcu.pwr_cap_0.2, mcu.pwr_cap_1.2, mcu.pwr_cap_2.2, mcu.pwr_cap_3.2, mcu.pwr_cap_4.2, mcu.pwr_cap_5.2, mcu.pwra_cap_0.2, mcu.pwra_cap_1.2, mcu.swclk_pull.1, mcu.vbat_cap.2, mcu.vref_cap_0.2, mcu.vref_cap_1.2, mcu.vref_cap_2.2, pwr_3v3.ic.1, pwr_3v3.in_cap.2, pwr_3v3.out_cap.2, pwr_5v.fb.bottom_res.2, pwr_5v.hf_in_cap.2, pwr_5v.ic.1, pwr_5v.in_cap.2, pwr_5v.out_cap.2, pwr_conn.1, pwr_conn.3, rtc.bbs_cap.2, rtc.ic.5, rtc.ic.8, rtc.vbat_cap.2, rtc.vdd_cap_0.2, rtc.vdd_cap_1.2, sd.3, sd.6, sd.SH, sw1.1, sw2.1, swd.3, swd.5, swd.9, usb_conn.A1B12, usb_conn.B1A12, v5sense.bottom_res.2, v12sense.bottom_res.2, vscsense.bottom_res.2, xbee.ic.10, xbee.ic.14, xbee.vdd_cap_0.2, xbee.vdd_cap_1.2, xbee_assoc.res.2
mcu.adc_2: mcu.ic.9, v5sense.bottom_res.1, v5sense.top_res.2
mcu.adc_3: mcu.ic.10, v12sense.bottom_res.1, v12sense.top_res.2
mcu.can_0.txd: can.transceiver.ic.3, mcu.ic.51
mcu.digital_1: mcu.ic.33, sw1.2, sw1_pull.2
mcu.digital_3: mcu.ic.39, rgb3.green_res.2
mcu.digital_4: mcu.ic.46, rgb3.red_res.2
mcu.digital_5: mcu.ic.25, rgb2.blue_res.2
mcu.digital_7: mcu.ic.28, rgb2.red_res.2
mcu.digital_9: mcu.ic.32, rgb1.green_res.2
mcu.digital_11: ext.6, mcu.ic.59
mcu.digital_13: eink.ic.13, mcu.ic.4
mcu.digital_14: eink.ic.14, mcu.ic.3
mcu.digital_15: eink.ic.15, mcu.ic.2
mcu.digital_16: eink.ic.16, mcu.ic.1
mcu.digital_19: mcu.ic.11, sd.1
mcu.spi_1.mosi: mcu.ic.15, sd.2
mcu.spi_1.sck: mcu.ic.17, sd.5
mcu.swd.reset: mcu.ic.45, mcu.reset_pull.2, swd.10
mcu.swd.swdio: mcu.ic.44, mcu.swdio_pull.2, swd.2
mcu.xtal.xtal_in: crystal.cap_a.1, crystal.package.1, mcu.ic.36
mcu.xtal.xtal_out: crystal.cap_b.1, crystal.package.3, mcu.ic.35
pwr_5v.fb.out: pwr_5v.fb.bottom_res.1, pwr_5v.fb.top_res.2, pwr_5v.ic.4
pwr_5v.sw: pwr_5v.ic.2, pwr_5v.inductor.1, pwr_5v.vbst_cap.2
pwr_5v.vbst_cap.pos: pwr_5v.ic.6, pwr_5v.vbst_cap.1
rgb1.blue: mcu.ic.30, rgb1.blue_res.2
rgb1.blue_res.a: rgb1.blue_res.1, rgb1.package.2
rgb1.green_res.a: rgb1.green_res.1, rgb1.package.3
rgb1.red: mcu.ic.31, rgb1.red_res.2
rgb1.red_res.a: rgb1.package.4, rgb1.red_res.1
rgb2.blue_res.a: rgb2.blue_res.1, rgb2.package.2
rgb2.green: mcu.ic.29, rgb2.green_res.2
rgb2.green_res.a: rgb2.green_res.1, rgb2.package.3
rgb2.red_res.a: rgb2.package.4, rgb2.red_res.1
rgb3.blue: mcu.ic.38, rgb3.blue_res.2
rgb3.blue_res.a: rgb3.blue_res.1, rgb3.package.2
rgb3.green_res.a: rgb3.green_res.1, rgb3.package.3
rgb3.red_res.a: rgb3.package.4, rgb3.red_res.1
rtc._bbs.pwr: rtc.bbs_cap.1, rtc.ic.14
rtc._vdd.pwr: rtc.ic.16, rtc.vdd_cap_0.1, rtc.vdd_cap_1.1, rtc.vdd_res.2
rtc.cs: mcu.ic.64, rtc.ic.4
rtc.pwr_bat: bat.1, rtc.ic.15, rtc.vbat_cap.1
rtc.spi.mosi: eink.ic.11, mcu.ic.6, rtc.ic.2
rtc.spi.sck: eink.ic.12, mcu.ic.5, rtc.ic.1
sd.spi.miso: mcu.ic.19, sd.7
sw2_pull.io: mcu.ic.23, sw2.2, sw2_pull.2
swd.swd.swclk: mcu.ic.40, mcu.swclk_pull.2, swd.4
swd.swd.swo: mcu.ic.12, swd.6
usb_conn.usb.dm: mcu.ic.48, usb_conn.A7, usb_conn.B7
usb_conn.usb.dp: mcu.ic.47, usb_conn.A6, usb_conn.B6
v3v3: can.transceiver.ic.1, can.transceiver.logic_cap.1, cd_pull.1, eink.boost_ind.1, eink.ic.9, eink.ic.10, eink.vdd_cap0.1, eink.vdd_cap1.1, ext.2, mcu.ic.13, mcu.ic.18, mcu.ic.20, mcu.ic.22, mcu.ic.37, mcu.ic.41, mcu.ic.52, mcu.ic.57, mcu.pwr_cap_0.1, mcu.pwr_cap_1.1, mcu.pwr_cap_2.1, mcu.pwr_cap_3.1, mcu.pwr_cap_4.1, mcu.pwr_cap_5.1, mcu.pwra_cap_0.1, mcu.pwra_cap_1.1, mcu.reset_pull.1, mcu.swdio_pull.1, mcu.vbat_cap.1, mcu.vref_cap_0.1, mcu.vref_cap_1.1, mcu.vref_cap_2.1, pwr_3v3.ic.2, pwr_3v3.out_cap.1, rgb1.package.1, rgb2.package.1, rgb3.package.1, rtc.vdd_res.1, sd.4, sw1_pull.1, sw2_pull.1, swd.1, xbee.ic.1, xbee.vdd_cap_0.1, xbee.vdd_cap_1.1
v5: buffer.amp.ic.5, buffer.amp.vdd_cap0.1, buffer.diode.1, buffer.sense.1, buffer.set.top_res.1, pwr_3v3.ic.3, pwr_3v3.in_cap.1, pwr_5v.fb.top_res.1, pwr_5v.inductor.2, pwr_5v.out_cap.1, usb_conn.A4B9, usb_conn.B4A9, v5sense.top_res.1
vin: pwr_5v.hf_in_cap.1, pwr_5v.ic.3, pwr_5v.ic.5, pwr_5v.in_cap.1, pwr_conn.2, v12sense.top_res.1
vscsense.center: mcu.ic.8, vscsense.bottom_res.1, vscsense.top_res.2
vscsense.pwr: buffer.cap.1, buffer.diode.2, buffer.fet.3, vscsense.top_res.1
xbee.associate: xbee.ic.15, xbee_assoc.package.2
xbee.data.rx: mcu.ic.58, xbee.ic.3
xbee.data.tx: mcu.ic.54, xbee.ic.2
xbee_assoc.res.a: xbee_assoc.package.1, xbee_assoc.res.1

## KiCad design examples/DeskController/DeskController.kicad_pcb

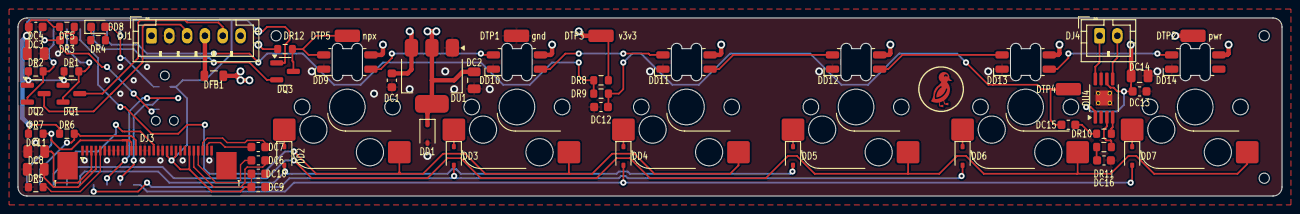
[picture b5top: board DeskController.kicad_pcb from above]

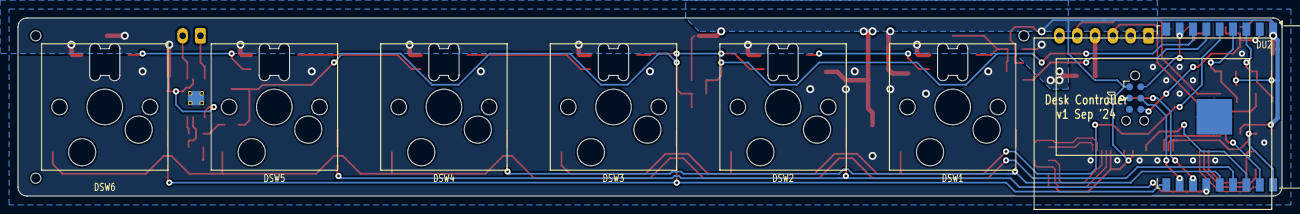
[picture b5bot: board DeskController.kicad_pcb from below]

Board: 2 copper layers, 142.0 x 20.0 mm, 69 parts (18 on the bottom side), 49 nets.

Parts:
DC1, DC4, DC13: 50V 100nF X7R ±10% 0603 Multilayer Ceramic Capaci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; C_0603_1608Metric
DC2, DC8: 25V 4.7uF X5R ±10% 0805 Multilayer Ceramic Capaci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; C_0805_2012Metric
DC3, DC11, DC14: 25V 10uF X5R ±10% 0805 Multilayer Ceramic Capacit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; C_0805_2012Metric
DC5, DC6, DC7, DC9, DC10, DC15, DC16: 50V 1uF X5R ±10% 0603 Multilayer Ceramic Capacito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; C_0603_1608Metric
DC12: 50V 33nF X7R ±10% 0603 Multilayer Ceramic Capacit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; C_0603_1608Metric
DD1: 3.6V~3.8V 200mW 3.6V SOD-323 Zener Diodes ROHS; D_SOD-323
DD2, DD3, DD4, DD5, DD6, DD7: 40V 600mV@1A 1A SOD-323 Schottky Diodes ROHS; D_SOD-323
DD8: -40?~+85? Red 0603 LED Indication - Discrete ROHS; LED_0603_1608Metric
DD9, DD10, DD11, DD12, DD13, DD14: SK6812MINI-E; LED_SK6812MINI-E
DFB1: ±25% 100?@100MHz 0805 Ferrite Beads ROHS; L_0805_2012Metric
DH1, DH2, DH3: JlcToolingHole_1.152mm
DJ1: B6B-PH-K; JST_PH_B6B-PH-K_1x06_P2.00mm_Vertical
DJ2: Tag-Connect_TC2030-IDC-NL_2x03_P1.27mm_Vertical
DJ3: AFC07-S30ECA-00; TE_3-1734839-0_1x30-1MP_P0.5mm_Horizontal
DJ4: B2B-PH-K; JST_PH_B2B-PH-K_1x02_P2.00mm_Vertical
DQ1, DQ2, DQ3: 30V 5.7A 26.5m?@10V,5.7A 1.4W 1.5V@250uA 1PCSNCha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; SOT-23
DR1, DR2, DR6, DR7, DR8, DR12: 100mW Thick Film Resistors 75V ±100ppm/? ±1% 4.7k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; R_0603_1608Metric
DR3: 100mW Thick Film Resistors 75V ±100ppm/? ±1% 10k?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; R_0603_1608Metric
DR4: 100mW Thick Film Resistors 75V ±100ppm/? ±1% 820?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; R_0603_1608Metric
DR5: 100mW Thick Film Resistors 75V ±100ppm/? ±1% 470k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; R_0603_1608Metric
DR9: 100mW Thick Film Resistors 75V ±100ppm/? ±1% 1k? 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; R_0603_1608Metric
DR10, DR11: 100mW Thick Film Resistors 75V ±100ppm/? ±1% 68k?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; R_0603_1608Metric
DSW1, DSW2, DSW3, DSW4, DSW5, DSW6: PG151101S11; SW_Hotswap_Kailh_MX
DTP1: gnd; TestPoint_TE_RCT_0805
DTP2: pwr; TestPoint_TE_RCT_0805
DTP3: v3v3; TestPoint_TE_RCT_0805
DTP4: spk_chain_1; TestPoint_TE_RCT_0805
DTP5: npx; TestPoint_TE_RCT_0805
DU1: LDL1117S33R; SOT-223-3_TabPin2
DU2: ESP32-C3-WROOM-02; ESP-WROOM-02
DU3: ER-OLED-0.96-1.1; Lcd_Er_Oled0.96_1.1_Outline
DU4: TPA2005D1; MSOP-8-1EP_3x3mm_P0.65mm_EP1.68x1.88mm_ThermalVias
svg2mod: G***; Symbol_DucklingSolid

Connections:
Dconn.dtx_shift.hv_io: DJ1.5, DQ1.3
Dconn.htx_shift.hv_io: DJ1.3, DQ2.3
Dconn.pwr: DFB1.1, DJ1.4
Dconn.uart.rx: DQ2.2, DR2.2, DU2.3
Dconn.uart.tx: DQ1.2, DR1.2, DU2.4
Dgnd: DC1.2, DC2.2, DC3.2, DC4.2, DC5.2, DC8.2, DC9.2, DC10.2, DC11.2, DC12.2, DC13.2, DC14.2, DC16.2, DD1.2, DD9.3, DD10.3, DD11.3, DD12.3, DD13.3, DD14.3, DJ1.2, DJ2.5, DJ3.1, DJ3.2, DJ3.6, DJ3.7, DJ3.8, DJ3.9, DJ3.10, DJ3.14, DJ3.15, DJ3.16, DJ3.18, DJ3.19, DJ3.21, DJ3.23, DJ3.30, DR4.2, DR5.2, DTP1.1, DU1.1, DU2.9, DU2.19, DU4.7, DU4.9
Di2c_pull.i2c.scl: DJ3.13, DR6.2, DU2.17
Di2c_pull.i2c.sda: DJ3.11, DJ3.12, DR7.2, DU2.18
Dledr.res.a: DD8.1, DR4.1
Dmcu.gpio.swc_0: DSW1.2, DSW2.2, DSW3.2, DU2.5
Dmcu.gpio.swc_1: DSW4.2, DSW5.2, DSW6.2, DU2.15
Dmcu.gpio.swr_0: DD2.2, DD5.2, DU2.14
Dmcu.gpio.swr_1: DD3.2, DD6.2, DU2.13
Dmcu.gpio.swr_2: DD4.2, DD7.2, DU2.10
Dmcu.program_boot_node: DD8.2, DJ2.2, DU2.8
Dmcu.program_en_node: DC5.1, DJ2.6, DR3.2, DU2.2
Dmcu.program_uart_node.a_tx: DJ2.3, DU2.12
Dmcu.program_uart_node.b_tx: DJ2.4, DU2.11
Dnpx.led[0].dout: DD9.2, DD10.4
Dnpx.led[1].dout: DD10.2, DD11.4
Dnpx.led[2].dout: DD11.2, DD12.4
Dnpx.led[3].dout: DD12.2, DD13.4
Dnpx.led[4].dout: DD13.2, DD14.4
Dnpx_shift.hv_io: DD9.4, DQ3.3, DR12.2, DTP5.1
Dnpx_shift.lv_io: DQ3.2, DU2.6
Doled.c1_cap.neg: DC6.2, DJ3.26
Doled.c1_cap.pos: DC6.1, DJ3.27
Doled.c2_cap.neg: DC7.2, DJ3.28
Doled.c2_cap.pos: DC7.1, DJ3.29
Doled.device.vcc: DC11.1, DJ3.3
Doled.device.vcomh: DC8.1, DJ3.4
Doled.iref_res.a: DJ3.5, DR5.1
Doled.reset: DJ3.17, DU2.16
Dpwr: DC1.1, DC13.1, DC14.1, DD9.1, DD10.1, DD11.1, DD12.1, DD13.1, DD14.1, DFB1.2, DR12.1, DTP2.1, DU1.3, DU4.1, DU4.6
Dspk_chain_0: DR8.2, DR9.1, DU2.7
Dspk_chain_1: DC12.1, DC15.2, DR9.2, DTP4.1
Dspk_chain_2.a: DJ4.1, DU4.8
Dspk_chain_2.b: DJ4.2, DU4.5
Dspk_drv.inn_cap.pos: DC16.1, DR11.1
Dspk_drv.inn_res.b: DR11.2, DU4.3
Dspk_drv.inp_cap.pos: DC15.1, DR10.1
Dspk_drv.inp_res.b: DR10.2, DU4.4
Dsw.d[0,0].cathode: DD2.1, DSW1.1
Dsw.d[0,1].cathode: DD3.1, DSW2.1
Dsw.d[0,2].cathode: DD4.1, DSW3.1
Dsw.d[1,0].cathode: DD5.1, DSW4.1
Dsw.d[1,1].cathode: DD6.1, DSW5.1
Dsw.d[1,2].cathode: DD7.1, DSW6.1
Dv3v3: DC2.1, DC3.1, DC4.1, DC9.1, DC10.1, DD1.1, DJ2.1, DJ3.20, DJ3.22, DJ3.25, DQ1.1, DQ2.1, DQ3.1, DR1.1, DR2.1, DR3.1, DR6.1, DR7.1, DR8.1, DTP3.1, DU1.2, DU2.1
